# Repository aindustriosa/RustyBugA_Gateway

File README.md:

# WiFi Serial Gateway for the [RustyBugA](https://github.com/aindustriosa/RustyBugA-board#)

Firmware and tools for a Seeed Studio XIAO C3 based serial gateway that uses WiFi as wireless interface.

# Usage
## Hardware connections
TBD

## Connect from the PC using USB (like an FTDI)
> Remember to remove the jumper when the USB cable is not connected.

Make all the connections and:
```
picocom /dev/ttyACM3 -b 115200
```
This interface also prints some internal logs from the gateway (like it's IP address at start).

## Connect from the PC using netcat (like an FTDI but wireless!)
> Remember to use the jumper when the USB cable is not connected.

Connect the PC to the same network as the gateway and use the mDNS name to create a connection:
```
nc -u ${MDNS_NAME}.local 1234
```
now data can be exchanged with the robot.

If you don't know the MDNS_NAME, it is printed over the USB link at start.

## Connect from the PC using tools
TBD

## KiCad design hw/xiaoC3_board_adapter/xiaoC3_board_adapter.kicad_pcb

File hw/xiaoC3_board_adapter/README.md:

# Tools

## PCB design, gerber files creation: KiCAD
Version 9
https://docs.kicad.org/9.0/en/getting_started_in_kicad/getting_started_in_kicad.html

## Gerber to png
https://gerber2png.fablabkerala.in/
https://git.fablabkerala.in/midlaj/gerber2png/-/wikis/home

## PNG to Gcode
https://modsproject.org/

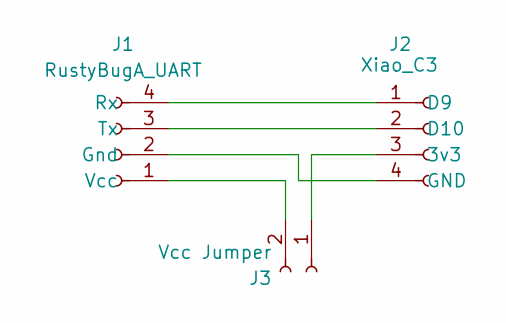
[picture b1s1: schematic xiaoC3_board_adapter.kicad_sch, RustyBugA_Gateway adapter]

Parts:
J1: RustyBugA_UART; PinHeader_1x04_P2.54mm_Vertical
J2: Xiao_C3; PinHeader_1x04_P2.54mm_Vertical
J3: Vcc Jumper; PinSocket_1x02_P2.54mm_Vertical

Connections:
unnamed: J1.2 (Gnd), J2.4 (GND)
unnamed: J1.4 (Rx), J2.1 (D9)
unnamed: J1.3 (Tx), J2.2 (D10)
unnamed: J1.1 (Vcc), J3.2
unnamed: J2.3 (3v3), J3.1

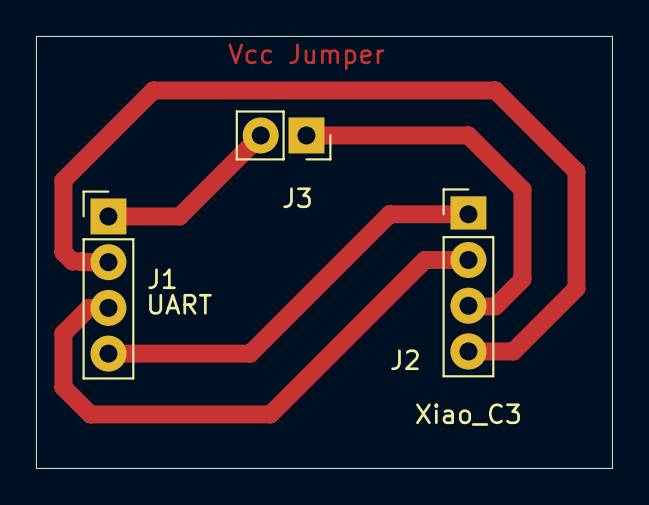
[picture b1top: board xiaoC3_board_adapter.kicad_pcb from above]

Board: 2 copper layers, 32.0 x 24.0 mm, 3 parts (0 on the bottom side), 5 nets.

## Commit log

2025-06-25 Add first version of the adaptation board
2025-07-02 Update PCB design and generate gcodes for first working version
2025-07-02 update docs
2025-07-09 Use USB port lika a gateway
